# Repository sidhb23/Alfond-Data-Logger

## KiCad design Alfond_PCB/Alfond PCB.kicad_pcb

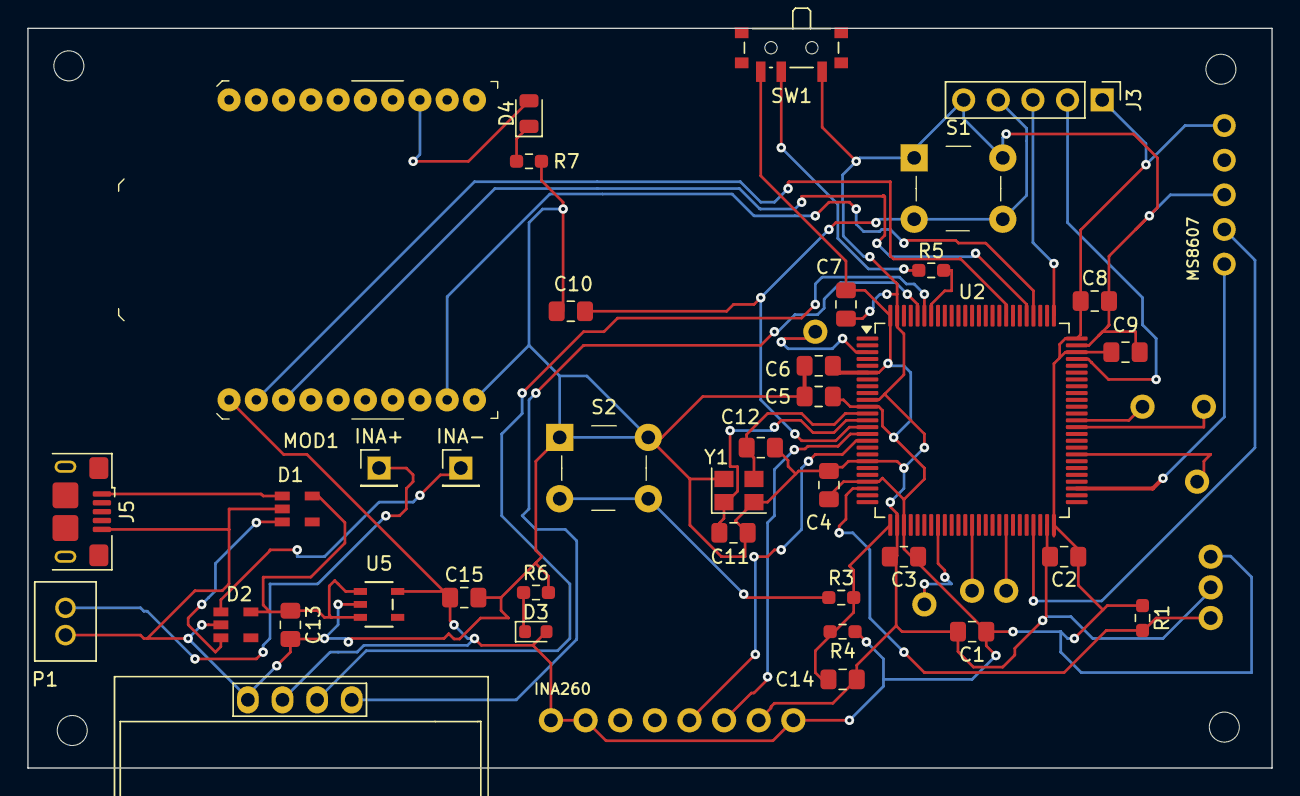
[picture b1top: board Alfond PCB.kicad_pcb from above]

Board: 2 copper layers, 91.2 x 54.2 mm, 44 parts (0 on the bottom side), 29 nets.

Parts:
Brd1: SSD1306; 128x64OLED
C1: 4u7; C_0805_2012Metric_Pad1.18x1.45mm_HandSolder
C2, C3, C4, C5, C6, C7, C8, C9, C10, C14: 100n; C_0805_2012Metric_Pad1.18x1.45mm_HandSolder
C11, C12: 10p; C_0805_2012Metric_Pad1.18x1.45mm_HandSolder
C13: 10u; C_0805_2012Metric_Pad1.18x1.45mm_HandSolder
C15: 2.2u; C_0805_2012Metric_Pad1.18x1.45mm_HandSolder
D1, D2: SOT-23-5
D3: RED; LED_0603_1608Metric
D4: RED; LED_0805_2012Metric
H1, H2, H3, H4: MountingHole; MountingHole_2.2mm_M2
INA260: 1X08_ROUND_70
INA+: PinHeader_1x01_P2.54mm_Vertical
INA-: PinHeader_1x01_P2.54mm_Vertical
J3: Conn_01x05_Pin; PinHeader_1x05_P2.54mm_Vertical
J5: USB_B_Micro; USB_Micro-B_Amphenol_10118193-0001LF_Horizontal
MOD1: XB24CZ7PIT-004; XBEE-20_THT
MS8607: 1X05_ROUND
P1: PHR-2; JST_PHR-2
R1: 4.7k; R_0603_1608Metric_Pad0.98x0.95mm_HandSolder
R3: 1k; R_0603_1608Metric_Pad0.98x0.95mm_HandSolder
R4, R5: 10k; R_0603_1608Metric_Pad0.98x0.95mm_HandSolder
R6, R7: 1.5k; R_0603_1608Metric_Pad0.98x0.95mm_HandSolder
S1, S2: PTS645SM43SMTR92_LFS; Switch_Tactile_THT_B3F-1xxx
SW1: SW_SPDT; SW_SPDT_PCM12
U2: STM32U545VETx; LQFP-100_14x14mm_P0.5mm
U5: MIC5219-3.3YM5-TR; SOT-23-5_M5_MCH
Y1: 16MHz; Crystal_SMD_3225-4Pin_3.2x2.5mm

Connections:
+3.3V: Brd1.2 (VCC), C1.1, C2.1, C3.1, C4.1, C5.1, C6.1, C7.1, C8.1, C9.1, C15.1, D3.2 (A), INA260.8, INA260.Vin+, INA260.Vin-, J3.1, MOD1.1 (Vcc), MS8607.5, R1.1, R4.1, SW1.3 (C), U2.6 (VBAT), U2.11 (VDD), U2.22 (VDDA), U2.28 (VDD), U2.50 (VDD), U2.73 (VDDUSB), U2.75 (VDD), U2.100 (VDD), U5.5 (OUT)
/BOOT0: R5.2, U2.94 (PH3)
/GPIO_INPUT_Button: C14.1, R3.2, R4.2, U2.26 (PA3)
/GPIO_SLEEP_XBEE: MOD1.9 (~DTR/SLRQ/DI8), U2.79 (PC11)
/HSE_IN: C12.1, U2.12 (PH0), Y1.3
/HSE_OUT: C11.1, U2.13 (PH1), Y1.1
/I2C1_SCL: Brd1.3 (SCL), U2.95 (PB8)
/I2C1_SDA: Brd1.4 (SDA), U2.96 (PB9)
/I2C2_SCL: MS8607.2, U2.47 (PB10)
/I2C2_SDA: MS8607.1, U2.53 (PB14)
/I2C3_SCL: INA260.6, U2.15 (PC0)
/I2C3_SDA: INA260.5, U2.16 (PC1)
/INA+: INA+.1, P1.2
/INA-: D2.1, INA-.1
/NRST: C10.1, J3.4, S1.3, S1.4, U2.14 (NRST)
/PWR_LED_K: D3.1 (K), R6.1
/PWR_LED_K2: D4.1 (K), R7.1
/SWD_CLK: J3.3, U2.76 (PA14)
/SWD_DIO: J3.2, U2.72 (PA13)
/UART4_TX: R1.2, U2.23 (PA0)
/UART5_RX: MOD1.2 (DOUT), U2.83 (PD2)
/UART5_TX: MOD1.3 (DIN/~Config), U2.80 (PC12)
/V_USB: D1.1, J5.1 (VBUS)
EN: D1.3, D2.3
GND: Brd1.1 (GND), C1.2, C2.2, C3.2, C4.2, C5.2, C6.2, C7.2, C8.2, C9.2, C10.2, C11.2, C12.2, C13.2, C14.2, C15.2, D1.2, D2.2, INA260.7, J3.5, J5.5 (GND), MOD1.10 (GND), MS8607.3, P1.1, R6.2, R7.2, S1.1, S1.2, S2.1, S2.2, SW1.1 (A), U2.10 (VSS), U2.19 (VSSA), U2.27 (VSS), U2.49 (VSS), U2.74 (VSS), U2.99 (VSS), U5.2 (GND), Y1.2, Y1.4
unnamed: C13.1, D1.5, D2.5, U5.1 (IN), U5.3 (EN)
unnamed: D4.2 (A), MOD1.13 (ON/~SLEEP)
unnamed: R3.1, S2.3, S2.4
unnamed: R5.1, SW1.2 (B)

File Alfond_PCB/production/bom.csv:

Designator,Footprint,Quantity,Value,LCSC Part #
"_7, _6, _5, _4, _3, _2, ",,7,,
BRD1,128x64OLED,1,SSD1306,
C1,0603,1,4u7,
"C10, C14, C2, C3, C4, C5, C6, C7, C8, C9",0402,10,100n,
"C11, C12",0402,2,10p,
C13,0805,1,10u,
C15,0805,1,2.2u,
"D1, D2",SOT-23-5,2,SOT-23-5,
D3,0603,1,RED,
D4,0805,1,RED,
"INA+, INA-",PinHeader_1x01_P2.54mm_Vertical,2,PinHeader_1x01_P2.54mm_Vertical,
INA260,1X08_ROUND_70,1,1X08_ROUND_70,
J3,PinHeader_1x05_P2.54mm_Vertical,1,Conn_01x05_Pin,
J5,USB_Micro-B_Wuerth_629105150521,1,USB_B_Micro,
MOD1,XBEE-20_THT,1,XB24CZ7PIT-004,XB24CZ7PIT-004
MS8607,1X05_ROUND,1,1X05_ROUND,
P1,JST_PHR-2,1,PHR-2,
R1,0402,1,4.7k,
R3,0402,1,1k,
"R4, R5",0402,2,10k,
"R6, R7",0402,2,1.5k,
"S1, S2",Switch_Tactile_THT_B3F-1xxx,2,PTS645SM43SMTR92_LFS,PTS645SM43SMTR92 LFS
SW1,SW_SPDT_PCM12,1,SW_SPDT,
U1,TO-92_Inline,1,DS18B20,
U2,LQFP-100_14x14mm_P0.5mm,1,STM32U545VETx,
U5,SOT-23-5_M5_MCH,1,MIC5219-3.3YM5-TR,
Y1,Crystal_SMD_3225-4Pin_3.2x2.5mm,1,16MHz,

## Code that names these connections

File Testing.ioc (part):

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Mcu.Name=STM32U545RETxQ
Mcu.Package=LQFP64
Mcu.UserName=STM32U545RETxQ
PA0.Mode=Half_duplex(single_wire_mode)
PA0.Signal=UART4_TX
PA5.Signal=GPIO_Output
PA7.Mode=Half_duplex(single_wire_mode)
PA7.Signal=USART3_TX
PB10.Mode=I2C
PB10.Signal=I2C2_SCL
PB14.Mode=I2C
PB14.Signal=I2C2_SDA
PB3\ (JTDO/TRACESWO).Mode=I2C
PB3\ (JTDO/TRACESWO).Signal=I2C1_SDA
PB6.Mode=I2C
PB6.Signal=I2C1_SCL
PC0.Mode=I2C
PC0.Signal=I2C3_SCL
PC1.Mode=I2C
PC1.Signal=I2C3_SDA
PC12.Mode=Asynchronous
PC12.Signal=UART5_TX
PC13.Signal=GPXTI13
PD2.Mode=Asynchronous
PD2.Signal=UART5_RX
PH0-OSC_IN\ (PH0).Mode=HSE-External-Oscillator
PH0-OSC_IN\ (PH0).Signal=RCC_OSC_IN
PH1-OSC_OUT\ (PH1).Mode=HSE-External-Oscillator
PH1-OSC_OUT\ (PH1).Signal=RCC_OSC_OUT
RCC.HSE_VALUE=16000000
RCC.SYSCLKFreq_VALUE=160000000
RCC.SYSCLKSource=RCC_SYSCLKSOURCE_PLLCLK
board=NUCLEO-U545RE-Q
boardIOC=true

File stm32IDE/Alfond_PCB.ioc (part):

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Mcu.Name=STM32U535VCTx
Mcu.Package=LQFP100
Mcu.UserName=STM32U535VCTx
PA0.Mode=Asynchronous
PA0.Signal=UART4_TX
PA1.Mode=Asynchronous
PA1.Signal=UART4_RX
PA11.Mode=Device
PA11.Signal=USB_DM
PA12.Mode=Device
PA12.Signal=USB_DP
PA13\ (JTMS/SWDIO).Mode=Serial_Wire
PA13\ (JTMS/SWDIO).Signal=DEBUG_JTMS-SWDIO
PA14\ (JTCK/SWCLK).Mode=Serial_Wire
PA14\ (JTCK/SWCLK).Signal=DEBUG_JTCK-SWCLK
PB3\ (JTDO/TRACESWO).Mode=I2C
PB3\ (JTDO/TRACESWO).Signal=I2C1_SDA
PB6.Mode=I2C
PB6.Signal=I2C1_SCL
PH0-OSC_IN\ (PH0).Mode=HSE-External-Oscillator
PH0-OSC_IN\ (PH0).Signal=RCC_OSC_IN
PH1-OSC_OUT\ (PH1).Mode=HSE-External-Oscillator
PH1-OSC_OUT\ (PH1).Signal=RCC_OSC_OUT
RCC.HSE_VALUE=16000000
board=custom

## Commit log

2024-09-27 Added the kicad files and stm32IDE files
2024-09-27 added kicad and stm32ide files and updated readme
2024-10-06 Removed stm32ide files because they were causing errors
2024-10-06 removed stm32ide files
2024-10-06 Updated kicad schematics
2024-10-06 Updated schematic with xbee, sd card slot and button
2024-10-07 added footprints to the symbols
2024-10-08 copy with the stm32u535
2024-10-08 saved copy with the stm32u535
2024-10-09 Changed MCU to STM32U545VET6
2024-10-23 Addedd STM32IDE Files
2024-10-26 Initial commit of STM32 project
2024-10-26 added Rpi Zigbee script
2024-11-21 Made the U545 project the primary project rather than zipping the project
2024-11-24 added the Raspberry Pi script to the new main branch and also added README
2024-11-24 updated README with a brief description
2024-11-24 changed project files to the most recent changes
2024-11-25 Further PCB design
    Found the issue with connecting adafruit through hole pins, and the rest of the PCB along with connecting more components
2024-11-26 updated Rpi script
2024-11-27 Removed layers
    Had extra copper layers that weren't used, and forgot to comment on the last push, but it was creating a fully connected pcb
2024-11-27 Footprints Used
    Added all the external footprints needed to properly view the PCB and schematic
2024-11-27 Updated the schematic and PCB
    The schematic and PCB had a generic MIC symbol and footprint, however the MIC that was ordered had 5 pins while the one in the PCB had 8.
2024-11-27 Delete Alfond_PCB (1) directory
    Added updated pcb changes, but it got added as a new directory and not changing the current one
2024-11-27 Update to PCB and Footprints
    The PCB was updated to the correct MIC ordered from Digikey, and the footprint was added to the footprint folders.
2024-11-28 fixed few errors
2024-11-28 PCB changes
    Added text for project name and group members, along with changing capacitor 14 from a footprint that wasn't working with one that is.
2024-11-28 Final PCB Changes
    Changed the Schottky diodes to the MAX40200 diodes
2024-11-28 Added test points
    Added test points for possible debugging of PCB
2024-12-11 Latest PCB Changes
    PCB changes for the PCB order that was made on 12/07/2024
2025-01-31 PCB order 2
2025-02-05 made improvments to pcb
2025-02-14 made changes to switch placement
2025-03-11 Final PCB Code
